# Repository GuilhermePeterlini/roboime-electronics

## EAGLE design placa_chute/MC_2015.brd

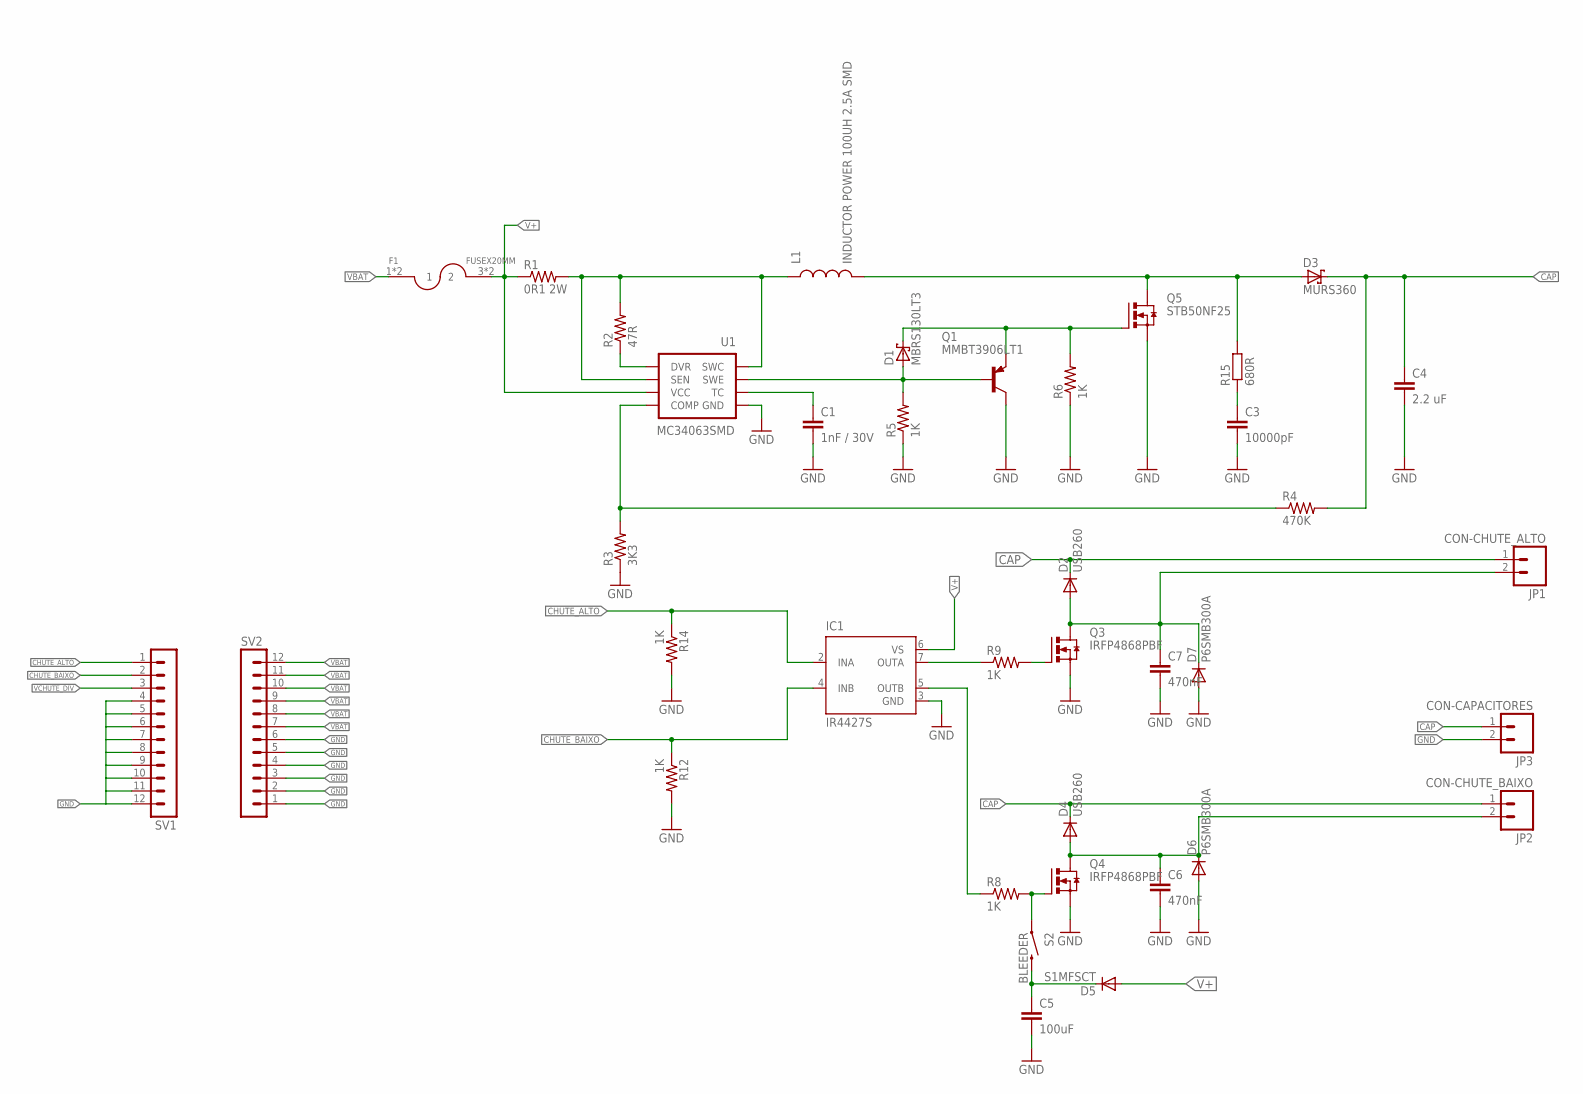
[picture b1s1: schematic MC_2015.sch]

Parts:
C1: 1nF / 30V; 0805
C3: 10000pF; 1210
C4: 2.2 uF; C2220K
C5: 100uF; C1210
C6, C7: 470nF; C1812
D1: MBRS130LT3; SMB
D2, D4: USB260; SMB
D3: MURS360; SMC
D5: S1MFSCT; SMA-DIODE
D6, D7: P6SMB300A; SMB
F1: FUSEX20MM; FUSE_5MM
IC1: IR4427S; SO08
JP1: CON-CHUTE_ALTO; SCREWTERMINAL-5MM-2
JP2: CON-CHUTE_BAIXO; SCREWTERMINAL-5MM-2
JP3: CON-CAPACITORES; SCREWTERMINAL-5MM-2
L1: INDUCTOR POWER 100UH 2.5A SMD; CDRH125
Q1: MMBT3906LT1; SOT23-BEC
Q3, Q4: IRFP4868PBF; TO247BV
Q5: STB50NF25; D2PACK
R1: 0R1 2W; R2512
R2: 47R; 0805
R3: 3K3; 0805
R4: 470K; R2512
R5, R6, R8, R9, R12, R14: 1K; 0805
R15: 680R; R1210
S2: BLEEDER; TACTILE-PTH
SV1, SV2: MA12-1
U1: MC34063SMD; SO08

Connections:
C3: C3.1, R15.1
CAP: C4.1, D2.C, D3.C, D4.C, JP1.1, JP2.1, JP3.1, R4.2
CHUTE_ALTO: IC1.2 (INA), R14.1, SV1.1
CHUTE_BAIXO: IC1.4 (INB), R12.1, SV1.2
GND: C1.2, C3.2, C4.2, C5.2, C6.2, C7.2, D6.A, D7.A, IC1.3 (GND), JP3.2, Q1.C, Q3.S, Q4.S, Q5.3 (S), R3.1, R5.1, R6.1, R12.2, R14.2, SV1.4, SV1.5, SV1.6, SV1.7, SV1.8, SV1.9, SV1.10, SV1.11, SV1.12, SV2.1, SV2.2, SV2.3, SV2.4, SV2.5, SV2.6, U1.4 (GND)
unnamed: IC1.5 (OUTB), R8.1
unnamed: L1.1, R1.2, R2.2, U1.1 (SWC), U1.7 (SEN)
unnamed: R2.1, U1.8 (DVR)
unnamed: C1.1, U1.3 (TC)
unnamed: R3.2, R4.1, U1.5 (COMP)
unnamed: Q4.G, R8.2, S2.1
unnamed: D3.A, L1.2, Q5.2 (D), R15.2
unnamed: D1.A, Q1.B, R5.2, U1.2 (SWE)
unnamed: C5.1, D5.C, S2.3 (2)
unnamed: D1.C, Q1.E, Q5.1 (G), R6.2
unnamed: IC1.7 (OUTA), R9.1
unnamed: Q3.G, R9.2
unnamed: C7.1, D2.A, D7.C, JP1.2, Q3.D
unnamed: C6.1, D4.A, D6.C, JP2.2, Q4.D
V+: D5.A, F1.3 (2), F1.4 (2), IC1.6 (VS), R1.1, U1.6 (VCC)
VBAT: F1.1, F1.2 (1), SV2.7, SV2.8, SV2.9, SV2.10, SV2.11, SV2.12
VCHUTE_DIV: SV1.3

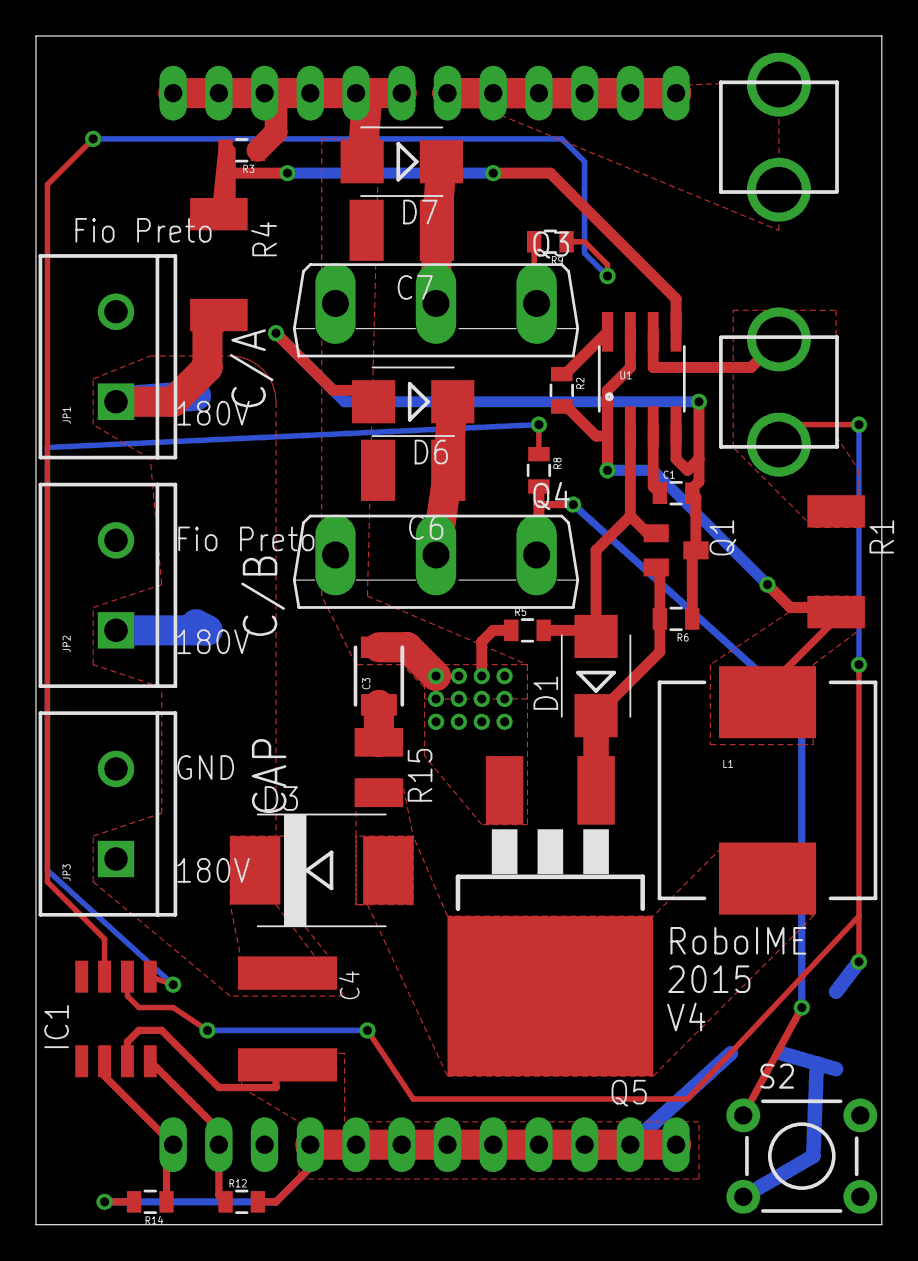
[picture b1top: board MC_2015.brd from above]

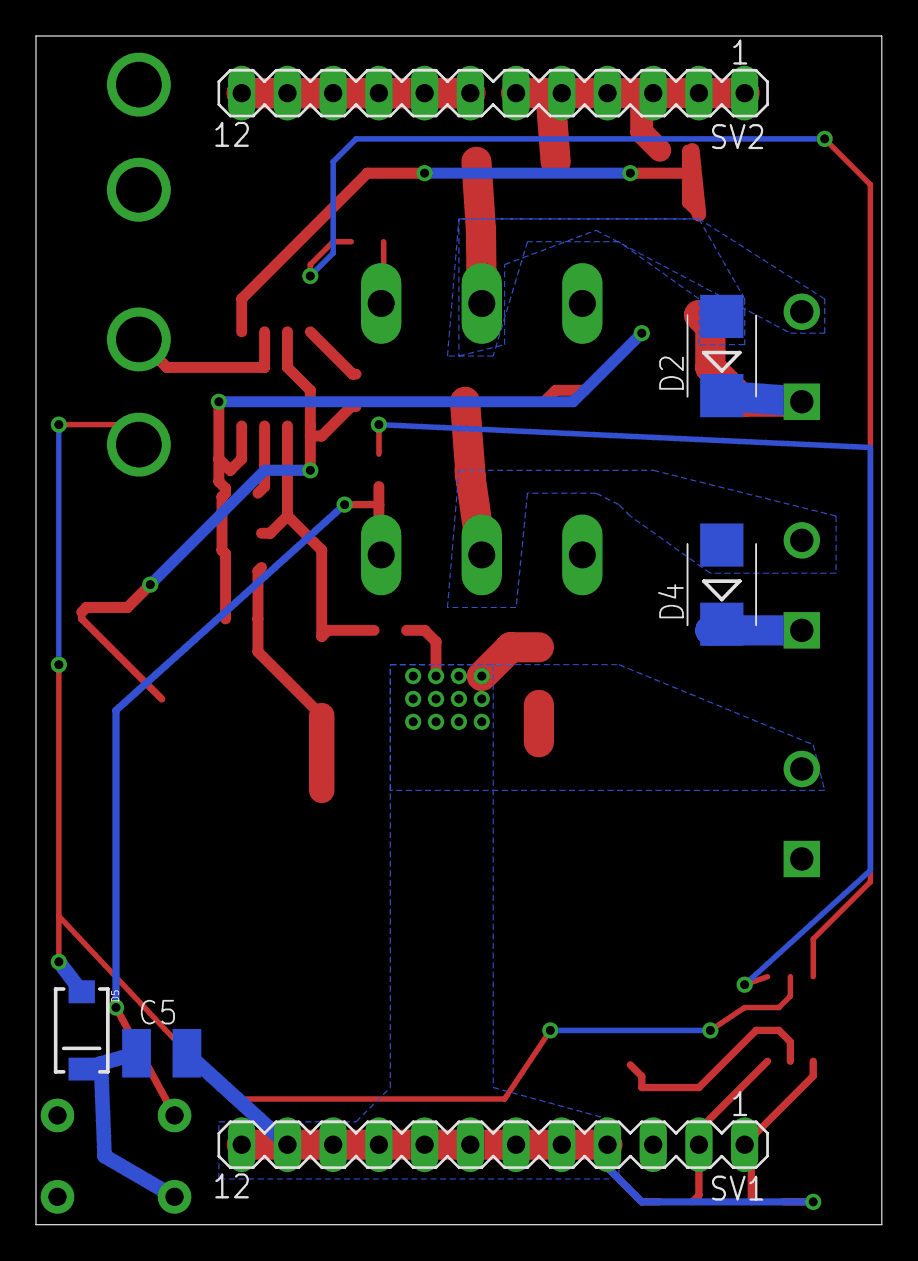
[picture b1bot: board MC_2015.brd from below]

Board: 2 copper layers, 47.0 x 66.0 mm, 38 parts (6 on the bottom side), 21 nets.

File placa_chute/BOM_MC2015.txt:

Partlist exported from C:/Users/lucasolim/Desktop/Circuitos/Placas 2/MC_2015/MC_2015.sch at 25/08/2014 16:57:39

Part Value                         Device                Package             Description                MF MPN OC_FARNELL OC_NEWARK
C1   1nF / 30V                     CAP0805               0805                Capacitor                                             
C3   10000pF                       CAP1210               1210                Capacitor                                             
C4   2.2 uF                        C-EUC2220K            C2220K              CAPACITOR, European symbol                            
C5   100uF                         C-EUC1210             C1210               CAPACITOR, European symbol                            
C6   470nF                         C-EUC1812             C1812               CAPACITOR, European symbol                            
C7   470nF                         C-EUC1812             C1812               CAPACITOR, European symbol                            
D1   MBRS130LT3                    MBRS130LT3            SMB                 Schottky Power Rectifier                              
D2   USB260                        DIODE-SMB             SMB                 DIODE                                                 
D3   MURS360                       SCHOTTKY-DIODESMC     SMC                 Schottky Diode                                        
D4   USB260                        DIODE-SMB             SMB                 DIODE                                                 
D5   S1MFSCT                       DIODESMA              SMA-DIODE           Diode                                                 
D6   P6SMB300A                     DIODE-SMB             SMB                 DIODE                                                 
D7   P6SMB300A                     DIODE-SMB             SMB                 DIODE                                                 
F1   FUSEX20MM                     FUSEX20MM             FUSE_5MM                                                                  
IC1  IR4427S                       IR4427S               SO08                DUAL LOW SIDE DRIVER                                  
JP1  CON-CHUTE_ALTO                M025MM                SCREWTERMINAL-5MM-2 Header 2                                              
JP2  CON-CHUTE_BAIXO               M025MM                SCREWTERMINAL-5MM-2 Header 2                                              
JP3  CON-CAPACITORES               M025MM                SCREWTERMINAL-5MM-2 Header 2                                              
L1   INDUCTOR POWER 100UH 2.5A SMD INDUCTORPWR           CDRH125             Inductors                                             
Q1   MMBT3906LT1                   MMBT3906LT1SMD        SOT23-BEC           PNP Transistror                                       
Q3   IRFP4868PBF                   IRFP240               TO247BV             HEXFET Power MosFet                                   
Q4   IRFP4868PBF                   IRFP240               TO247BV             HEXFET Power MosFet                                   
Q5   STB50NF25                     IRF3704S              D2PACK              SMPS MOSFET                                           
R1   0R1 2W                        RESISTOR2512          R2512               Resistor                                              
R2   47R                           RESISTOR              0805                Resistor                                              
R3   3K3                           RESISTOR              0805                Resistor                                              
R4   470K                          RESISTOR2512          R2512               Resistor                                              
R5   1K                            RESISTOR              0805                Resistor                                              
R6   1K                            RESISTOR              0805                Resistor                                              
R8   1K                            RESISTOR              0805                Resistor                                              
R9   1K                            RESISTOR0805-RES      0805                Resistor                                              
R12  1K                            RESISTOR              0805                Resistor                                              
R14  1K                            RESISTOR              0805                Resistor                                              
R15  680R                          R-EU_R1210            R1210               RESISTOR, European symbol                             
S2   BLEEDER                       SWITCH-MOMENTARY-2PTH TACTILE-PTH                                                               
SV1                                MA12-1                MA12-1              PIN HEADER                        unknown    unknown  
SV2                                MA12-1                MA12-1              PIN HEADER                        unknown    unknown  
U1   MC34063SMD                    MC34063SMD            SO08

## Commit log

2015-03-15 added placa de chute

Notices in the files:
parts and their libraries:
SparkFun-Passives: Licensing: CC v3.0 Share-Alike You are welcome to use this library for commercial purposes.
